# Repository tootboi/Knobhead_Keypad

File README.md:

# Knobhead Keypad
### Multi-functional custom Keypad

This project uses a Pro Micro with an ATmega32U4 on board. It allows the user to configure and use the rotary encoder, 9 mechanical switches and 3 rgb LEDs in many different ways, such as:
- Media keys (e.g. volume control, play/pause, ...)
- Macro keys (e.g. ctrl + Z, ctrl + shift + esc, ...)
- Mouse control (e.g. moving the cursor, middle click, ...)
- Keypad layer control
- Change LED colour and function

## Components
- 1x Pro Micro
- 1x EC11 rotary encoder
- 9x mechanical switches
- 9x Kailh hotswap sockets
- 9x 1N4148 diodes
- 1x 28mm diameter aluminium knob OR a 3D printed knob
- 1x 3D printed case

## PCB
Autodesk Eagle files needed to view the pcb design is in Knobhead_Keypad/src/pcb/ directory.

### Schematic

### Snapshot of pcb

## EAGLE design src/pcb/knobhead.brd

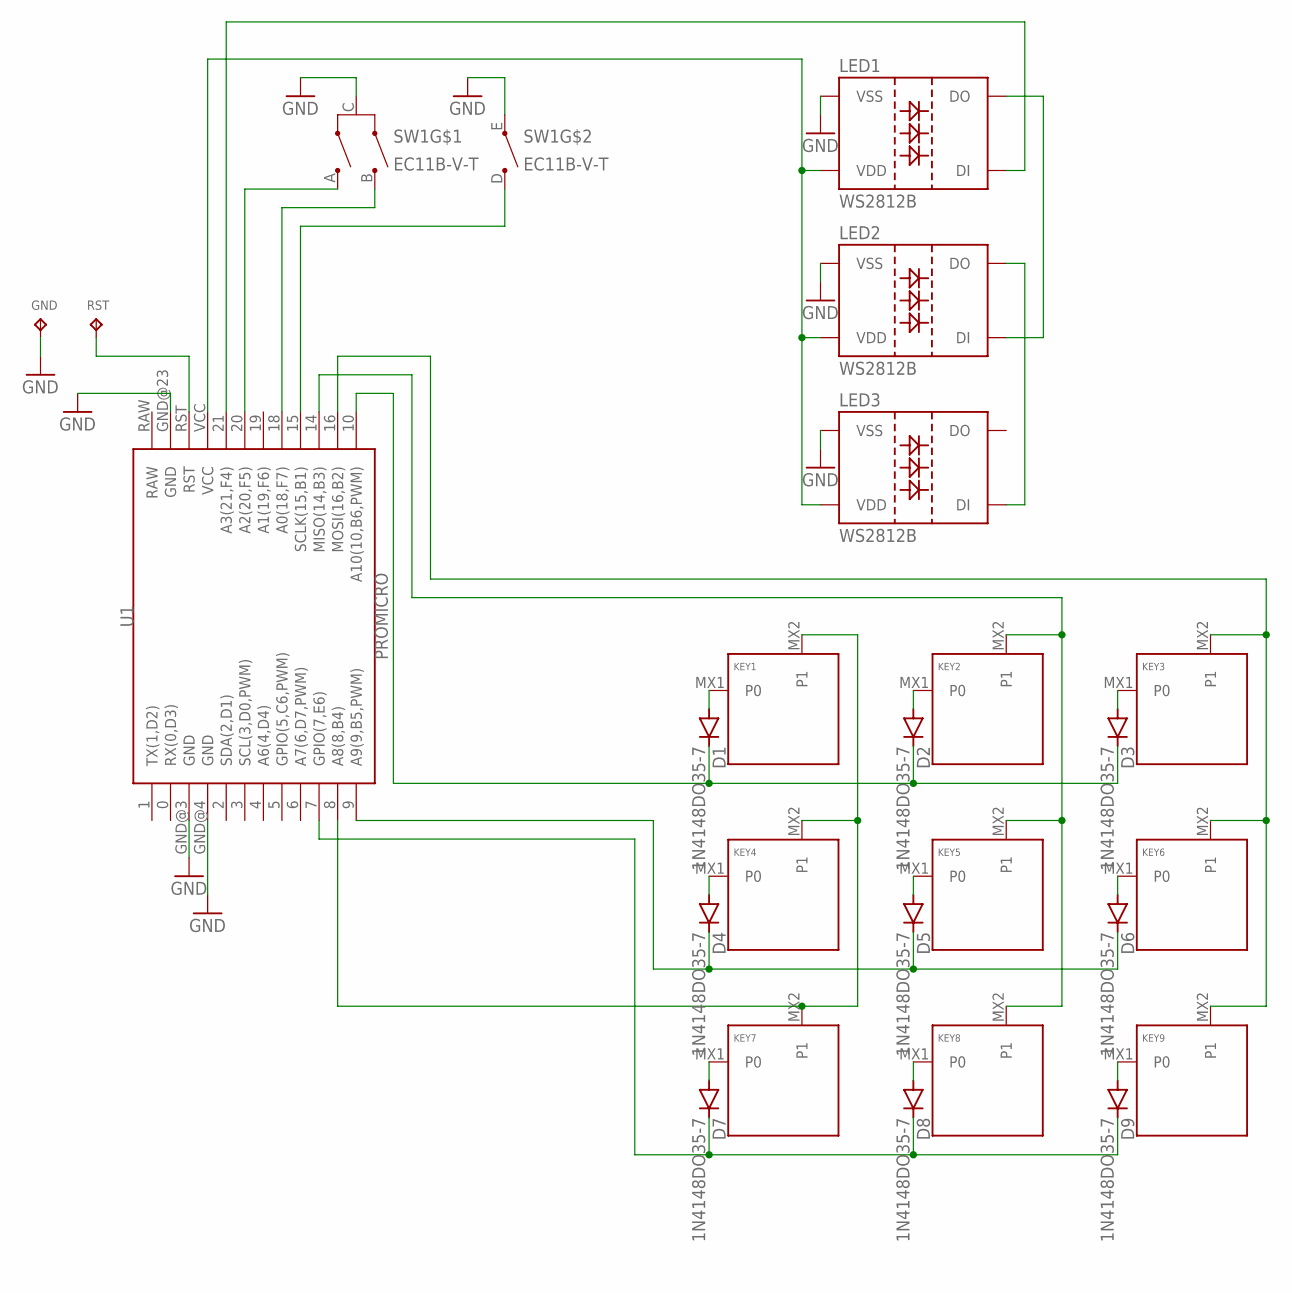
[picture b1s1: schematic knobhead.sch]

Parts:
D1, D2, D3, D4, D5, D6, D7, D8, D9: 1N4148DO35-7; DO35-7
GND: TPB1,27; B1,27
KEY1, KEY2, KEY3, KEY4, KEY5, KEY6, KEY7, KEY8, KEY9: KEYSWITCH-PLAIN-MXHSPCB-1U; MXHSPCB-1U
LED1, LED2, LED3: WS2812B
RST: TPB1,27; B1,27
SW1: EC11B-V-T; EC11B-V
U1: PROMICRO

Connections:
GND: GND.TP, LED1.3 (VSS), LED2.3 (VSS), LED3.3 (VSS), SW1.C, SW1.E, U1.GND@3 (GND), U1.GND@4 (GND), U1.GND@23 (GND)
unnamed: D1.A, KEY1.MX1 (P0)
unnamed: D2.A, KEY2.MX1 (P0)
unnamed: D3.A, KEY3.MX1 (P0)
unnamed: D4.A, KEY4.MX1 (P0)
unnamed: D5.A, KEY5.MX1 (P0)
unnamed: D6.A, KEY6.MX1 (P0)
unnamed: D7.A, KEY7.MX1 (P0)
unnamed: D8.A, KEY8.MX1 (P0)
unnamed: D9.A, KEY9.MX1 (P0)
unnamed: D1.C, D2.C, D3.C, U1.10 (A10(10,B6,PWM))
unnamed: D4.C, D5.C, D6.C, U1.9 (A9(9,B5,PWM))
unnamed: D7.C, D8.C, D9.C, U1.7 (GPIO(7,E6))
unnamed: KEY1.MX2 (P1), KEY4.MX2 (P1), KEY7.MX2 (P1), U1.8 (A8(8,B4))
unnamed: KEY2.MX2 (P1), KEY5.MX2 (P1), KEY8.MX2 (P1), U1.14 (MISO(14,B3))
unnamed: KEY3.MX2 (P1), KEY6.MX2 (P1), KEY9.MX2 (P1), U1.16 (MOSI(16,B2))
unnamed: LED1.1 (VDD), LED2.1 (VDD), LED3.1 (VDD), U1.VCC
unnamed: LED1.4 (DI), U1.21 (A3(21,F4))
unnamed: LED1.2 (DO), LED2.4 (DI)
unnamed: LED2.2 (DO), LED3.4 (DI)
unnamed: SW1.A, U1.20 (A2(20,F5))
unnamed: SW1.B, U1.18 (A0(18,F7))
unnamed: SW1.D, U1.15 (SCLK(15,B1))
unnamed: RST.TP, U1.RST

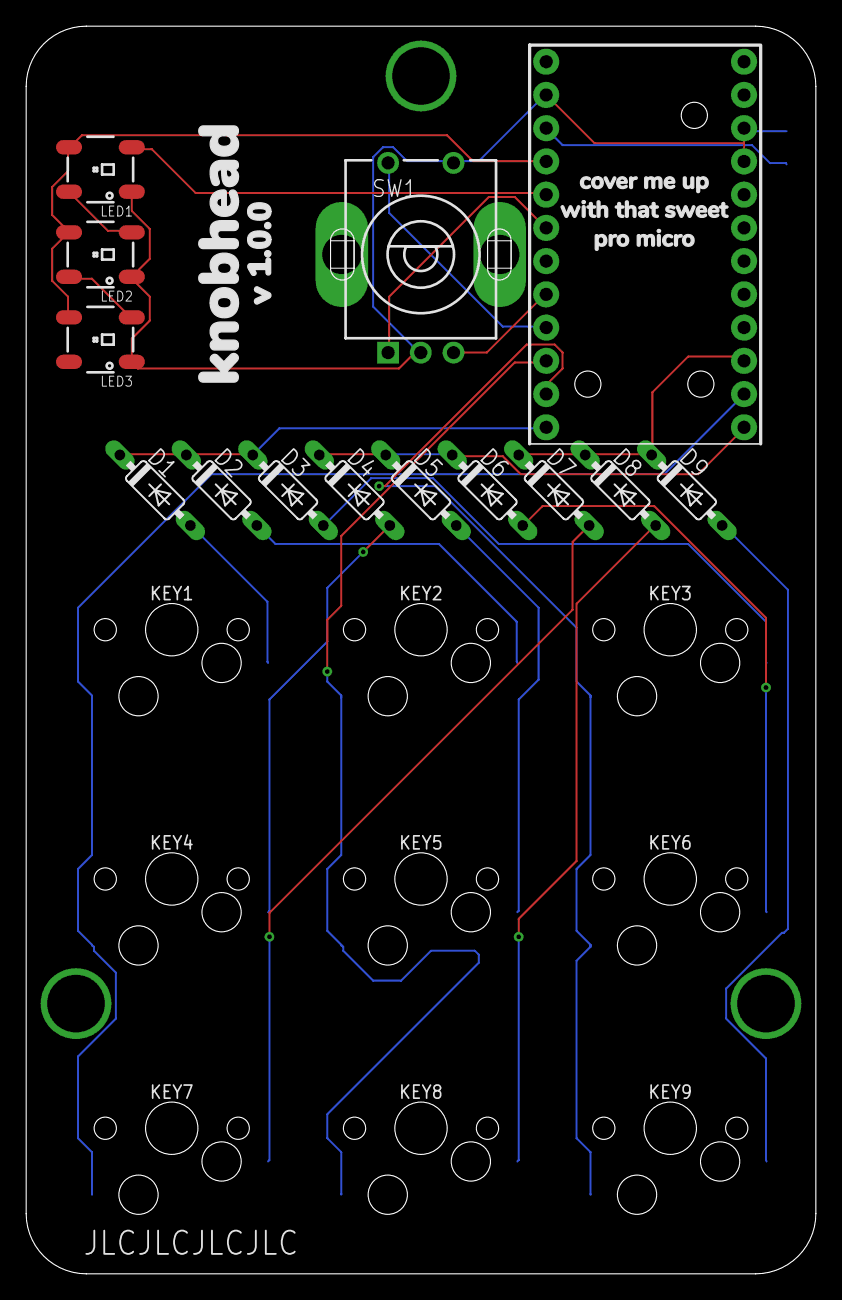
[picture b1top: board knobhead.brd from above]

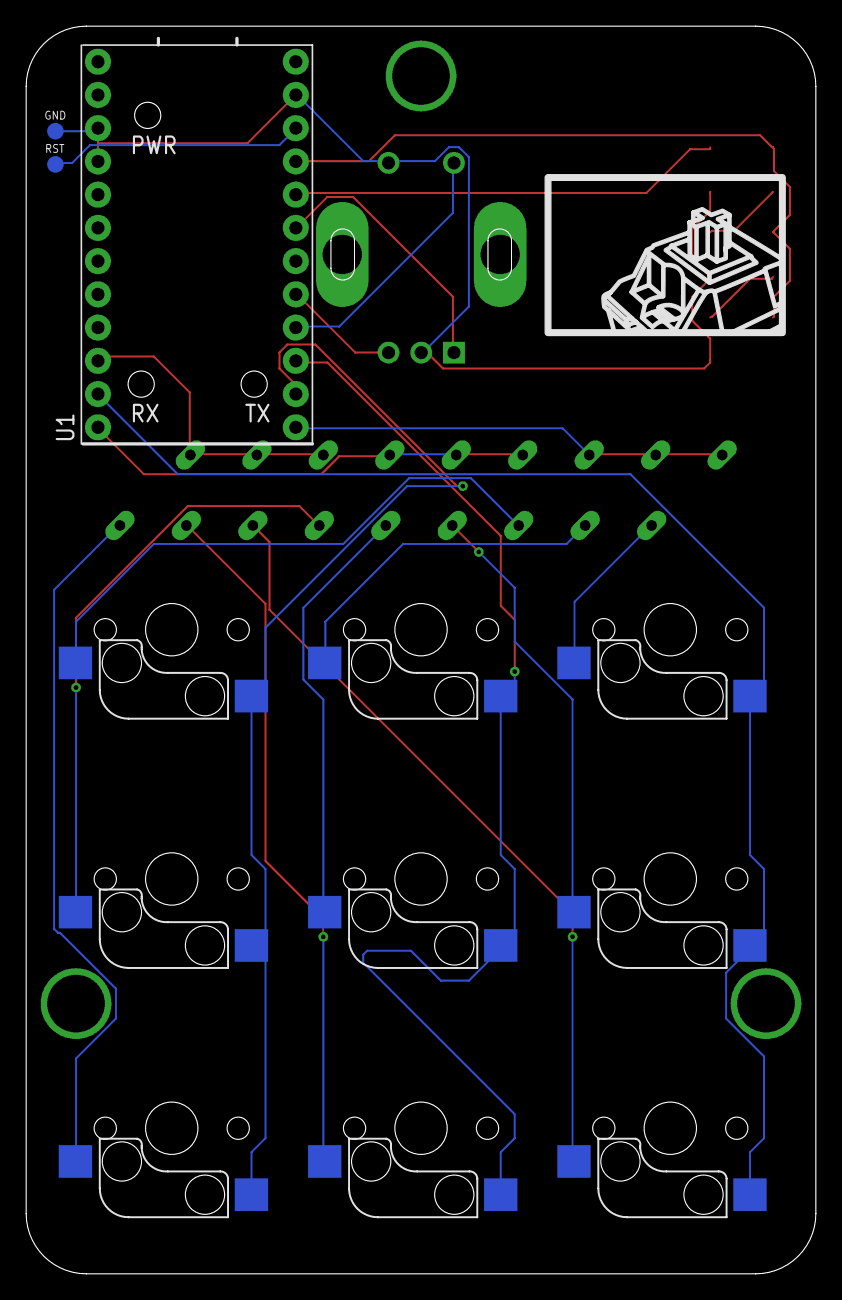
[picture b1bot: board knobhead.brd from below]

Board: 2 copper layers, 60.4 x 95.3 mm, 25 parts (12 on the bottom side), 24 nets.

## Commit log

2020-08-25 capsLock LED implemented
2020-08-26 double clicking with encoder implemented
2020-08-26 implemented layers to keypad
2020-08-28 fixed bug where encoder button presses will somtimes have ghost presses
2020-08-28 implemented long press
2020-08-29 removed Keypad library and implemented own function
2020-08-30 implemented layers for the rotary encoder
2020-09-11 implemented getEncoderDirection function
2020-09-11 implemented functionality to hold and rotate rotary encoder
2020-09-26 now uses an led strip instead of individual leds
2020-09-28 reduced pulseDebounce for more responsive rotary encoder. And minor code refactoring
2020-09-28 encoder button now has layers
2020-09-28 implemented sublayers
2020-10-09 cleaned up code and added sublayers to all components
2020-10-11 made code more modular
2020-10-23 edited some variables so it works with pcb and now uses row scan matrix
2021-01-09 fixed noisy rotary encoder output
2021-01-11 debugging for rotary encoder
2021-01-11 improved keypad matrix
2021-01-11 adjusted buffer and freq threshold and added code to make it easier to debug kepad
2021-01-12 implemented timeout for LED's
2021-01-13 cleaned up code for clickType and made it into a function
2021-01-13 added rainbow timeout animation
2021-07-27 uploaded pcb related material
2021-07-27 moved images to appropriate folder
2021-07-31 added stl files
